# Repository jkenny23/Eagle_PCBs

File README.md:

# Synchronous Test Board
PCB to test the EG2131 bootstrapping synchronous gate driver. Ended up switching to FD2203S which has same footprint/pinout but better performance. Board includes headers for switching Vin/Vout, power supply to gate driver (12V), Lin/Hin control for gate drive, positions for gate resistors (and pads to probe to indirectly measure gate drive current), positions for input and output shunt resistors (and associated pads) for measuring input/output current and voltage.

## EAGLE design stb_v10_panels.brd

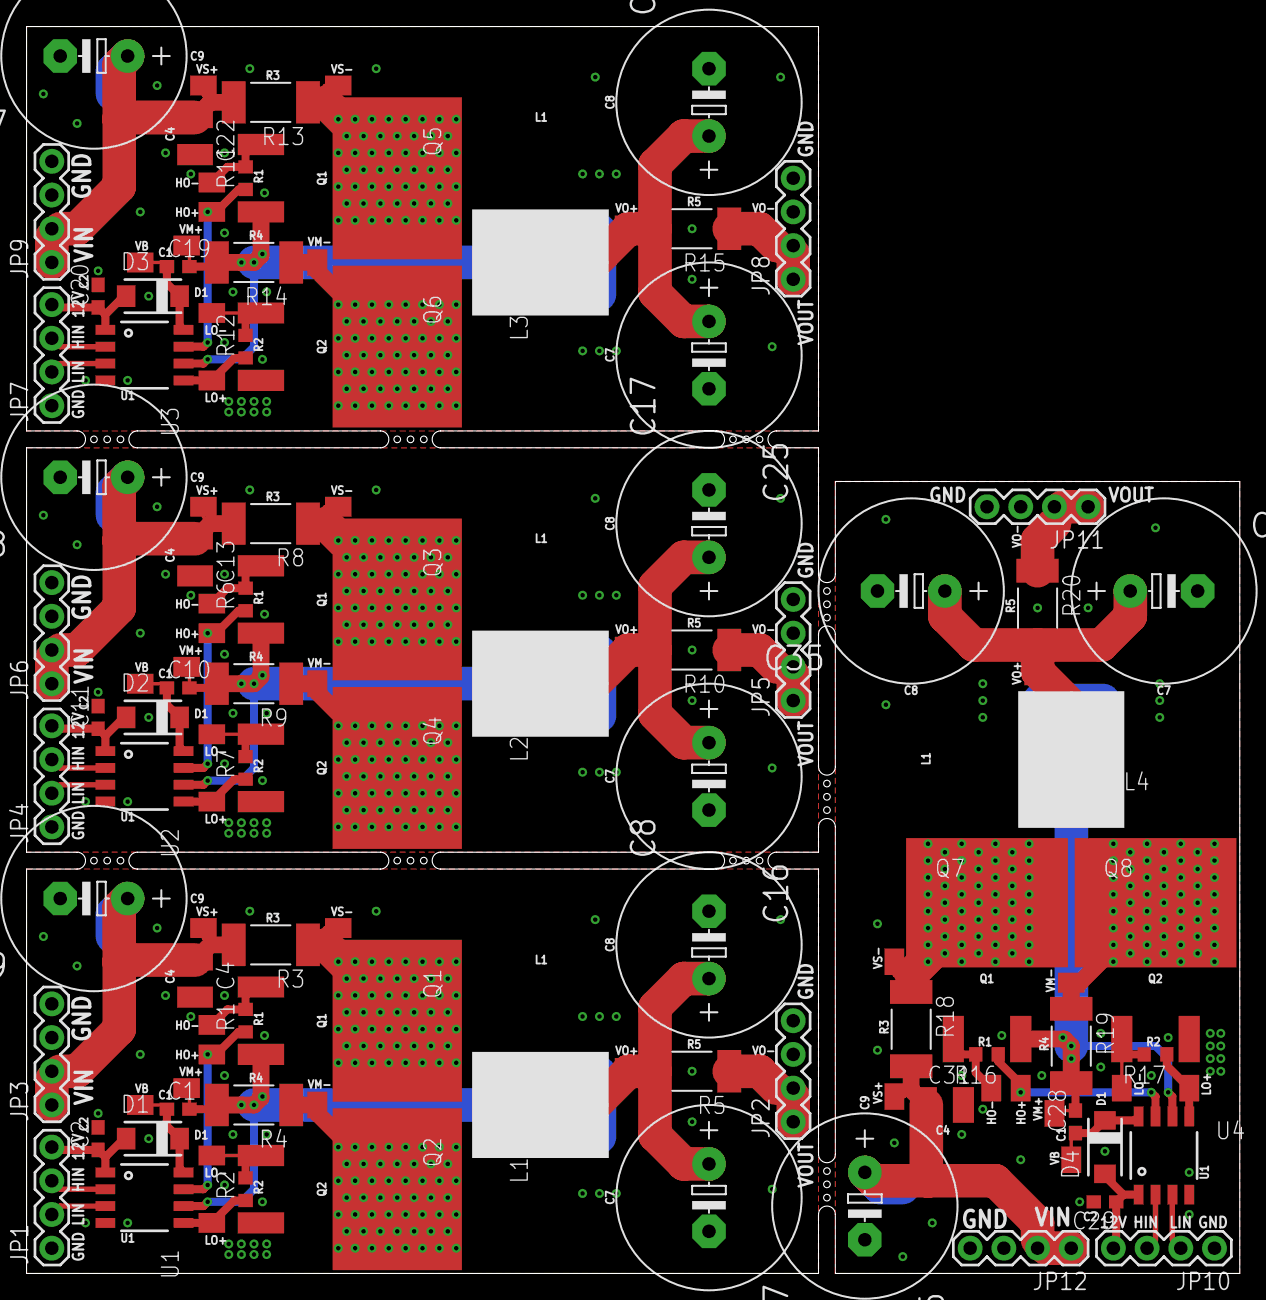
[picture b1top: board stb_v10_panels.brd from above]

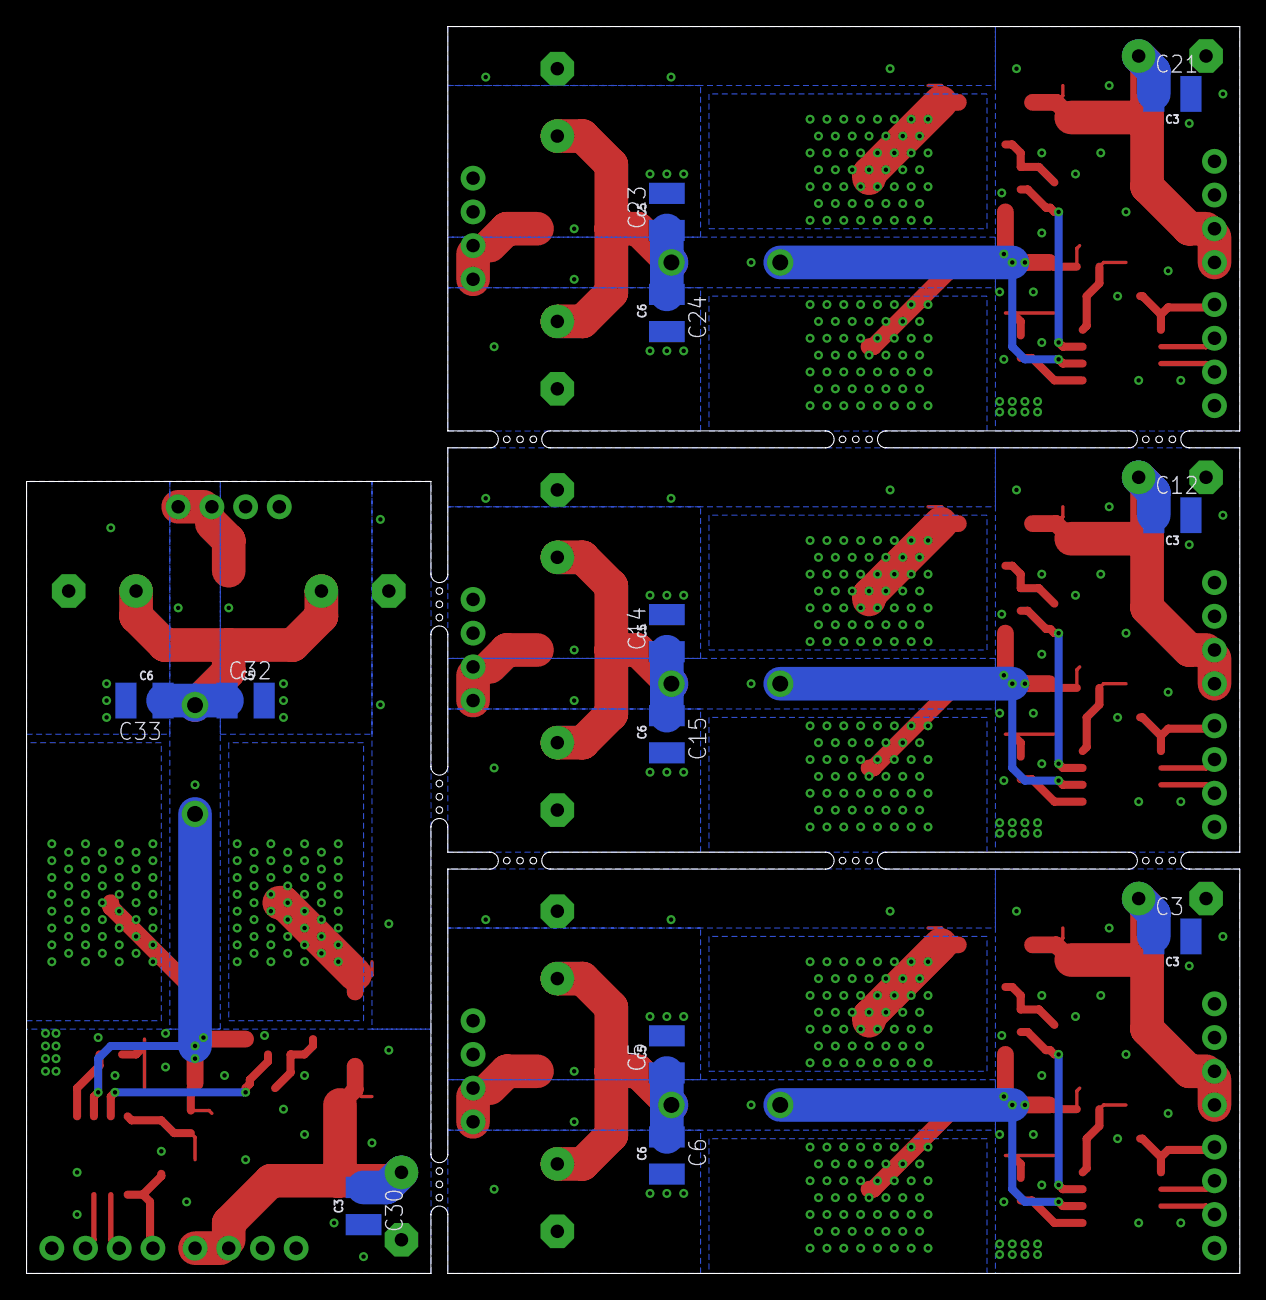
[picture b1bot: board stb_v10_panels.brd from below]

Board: 2 copper layers, 91.4 x 94.0 mm, 132 parts (12 on the bottom side), 60 nets.

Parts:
C1, C10, C19, C28: 10u; C0603
C2, C11, C20, C29: 100n; C0603
C3, C4, C5, C6, C12, C13, C14, C15, C21, C22, C23, C24, C30, C31, C32, C33: 2.2u; C1210
C7, C8, C9, C16, C17, C18, C25, C26, C27, C34, C35, C36: 220u; E5-13
D1, D2, D3, D4: SS54; SMA
JP1, JP2, JP3, JP4, JP5, JP6, JP7, JP8, JP9, JP10, JP11, JP12: 1X04
L1, L2, L3, L4: 60u; INDUCTOR_10A_8.2MMX21MM
Q1, Q2, Q3, Q4, Q5, Q6, Q7, Q8: STB4XN30M5; D2PAK-ST
R1, R2, R6, R7, R11, R12, R16, R17: 50m; R0603
R3, R4, R5, R8, R9, R10, R13, R14, R15, R18, R19, R20: 5m; R2512
TP1, TP2, TP3, TP4, TP5, TP6, TP7, TP8, TP9, TP10, TP11, TP12, TP13, TP14, TP15, TP16, TP17, TP18, TP19, TP20, TP21, TP22, TP23, TP24, TP25, TP26, TP27, TP28, TP29, TP30, TP31, TP32, TP33, TP34, TP35, TP36, TP37, TP38, TP39, TP40, TP41, TP42, TP43, TP44: TPADMEDIUM; TPAD_MED
U1, U2, U3, U4: EG2131; 8-SOIC

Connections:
12V: C2.1, D1.A, JP1.4, U1.1
12V1: C11.1, D2.A, JP4.4, U2.1
12V2: C20.1, D3.A, JP7.4, U3.1
12V3: C29.1, D4.A, JP10.4, U4.1
GND: C2.2, C3.2, C4.2, C5.2, C6.2, C7.-, C8.-, C9.-, JP1.1, JP2.3, JP2.4, JP3.3, JP3.4, Q2.3-S, U1.4
GND1: C11.2, C12.2, C13.2, C14.2, C15.2, C16.-, C17.-, C18.-, JP4.1, JP5.3, JP5.4, JP6.3, JP6.4, Q4.3-S, U2.4
GND2: C20.2, C21.2, C22.2, C23.2, C24.2, C25.-, C26.-, C27.-, JP7.1, JP8.3, JP8.4, JP9.3, JP9.4, Q6.3-S, U3.4
GND3: C29.2, C30.2, C31.2, C32.2, C33.2, C34.-, C35.-, C36.-, JP10.1, JP11.3, JP11.4, JP12.3, JP12.4, Q8.3-S, U4.4
HIN: JP1.3, U1.2
HIN1: JP4.3, U2.2
HIN2: JP7.3, U3.2
HIN3: JP10.3, U4.2
HO: R1.1, TP1.1, U1.7
HO1: R6.1, TP12.1, U2.7
HO2: R11.1, TP23.1, U3.7
HO3: R16.1, TP34.1, U4.7
LIN_N: JP1.2, U1.3
LIN_N1: JP4.2, U2.3
LIN_N2: JP7.2, U3.3
LIN_N3: JP10.2, U4.3
LO: R2.1, TP5.1, U1.5
LO1: R7.1, TP16.1, U2.5
LO2: R12.1, TP27.1, U3.5
LO3: R17.1, TP38.1, U4.5
VBST: C1.1, D1.K, TP9.1, U1.8
VBST1: C10.1, D2.K, TP20.1, U2.8
VBST2: C19.1, D3.K, TP31.1, U3.8
VBST3: C28.1, D4.K, TP42.1, U4.8
VGH: Q1.1-G, R1.2, TP2.1
VGH1: Q3.1-G, R6.2, TP13.1
VGH2: Q5.1-G, R11.2, TP24.1
VGH3: Q7.1-G, R16.2, TP35.1
VGL: Q2.1-G, R2.2, TP6.1
VGL1: Q4.1-G, R7.2, TP17.1
VGL2: Q6.1-G, R12.2, TP28.1
VGL3: Q8.1-G, R17.2, TP39.1
VMID: C1.2, L1.P$1, Q1.3-S, R4.2, TP7.1, U1.6
VMID1: C10.2, L2.P$1, Q3.3-S, R9.2, TP18.1, U2.6
VMID2: C19.2, L3.P$1, Q5.3-S, R14.2, TP29.1, U3.6
VMID3: C28.2, L4.P$1, Q7.3-S, R19.2, TP40.1, U4.6
VMID_SNS: Q2.2-D, R4.1, TP8.1
VMID_SNS1: Q4.2-D, R9.1, TP19.1
VMID_SNS2: Q6.2-D, R14.1, TP30.1
VMID_SNS3: Q8.2-D, R19.1, TP41.1
VO: JP2.1, JP2.2, R5.1, TP11.1
VO1: JP5.1, JP5.2, R10.1, TP22.1
VO2: JP8.1, JP8.2, R15.1, TP33.1
VO3: JP11.1, JP11.2, R20.1, TP44.1
VO_RAW: C5.1, C6.1, C7.+, C8.+, L1.P$2, R5.2, TP10.1
VO_RAW1: C14.1, C15.1, C16.+, C17.+, L2.P$2, R10.2, TP21.1
VO_RAW2: C23.1, C24.1, C25.+, C26.+, L3.P$2, R15.2, TP32.1
VO_RAW3: C32.1, C33.1, C34.+, C35.+, L4.P$2, R20.2, TP43.1
VS: C3.1, C4.1, C9.+, JP3.1, JP3.2, R3.2, TP3.1
VS1: C12.1, C13.1, C18.+, JP6.1, JP6.2, R8.2, TP14.1
VS2: C21.1, C22.1, C27.+, JP9.1, JP9.2, R13.2, TP25.1
VS3: C30.1, C31.1, C36.+, JP12.1, JP12.2, R18.2, TP36.1
VS_SNS: Q1.2-D, R3.1, TP4.1
VS_SNS1: Q3.2-D, R8.1, TP15.1
VS_SNS2: Q5.2-D, R13.1, TP26.1
VS_SNS3: Q7.2-D, R18.1, TP37.1

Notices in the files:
parts and their libraries:
SparkFun: Licensing: CC v3.0 Share-Alike You are welcome to use this library for commercial purposes.
